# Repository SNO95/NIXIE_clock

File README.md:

# NIXIE_clock
ATmega328p and DS3231 based nixie clock.
PCBs are from JLC PCB, the first version had some errors (pictures are the first version, the battery hodlers silk screen was off by 0.5mm and the p channel mosfets in the h bridge were wired wrong, and I forgot the reset pullup on the ATmega) but I think they are fixed now. If you find anything please let me know.

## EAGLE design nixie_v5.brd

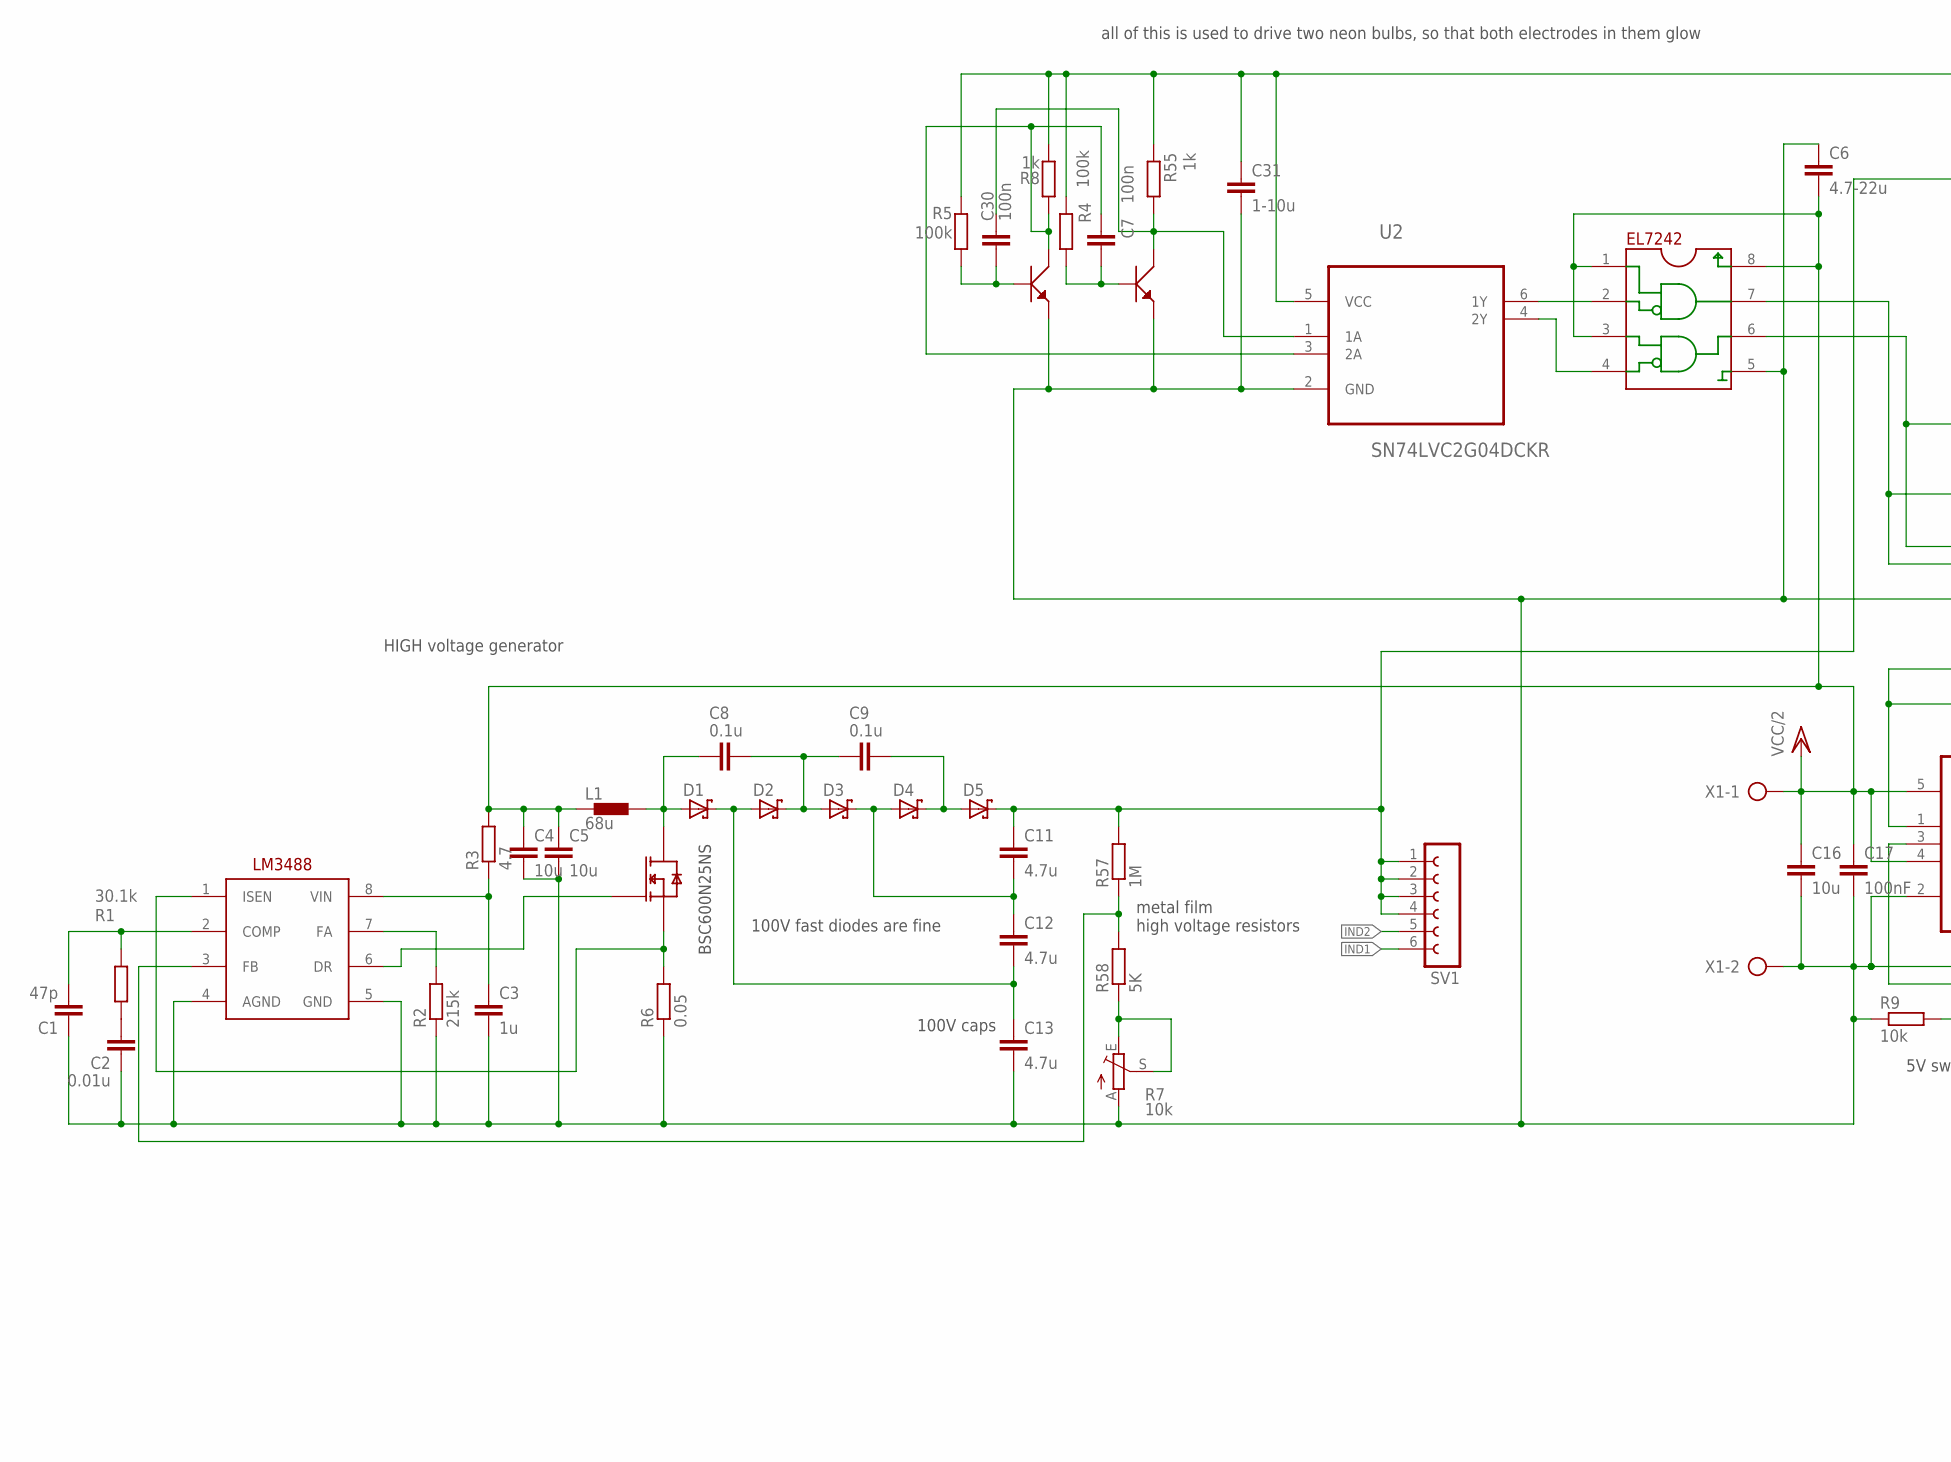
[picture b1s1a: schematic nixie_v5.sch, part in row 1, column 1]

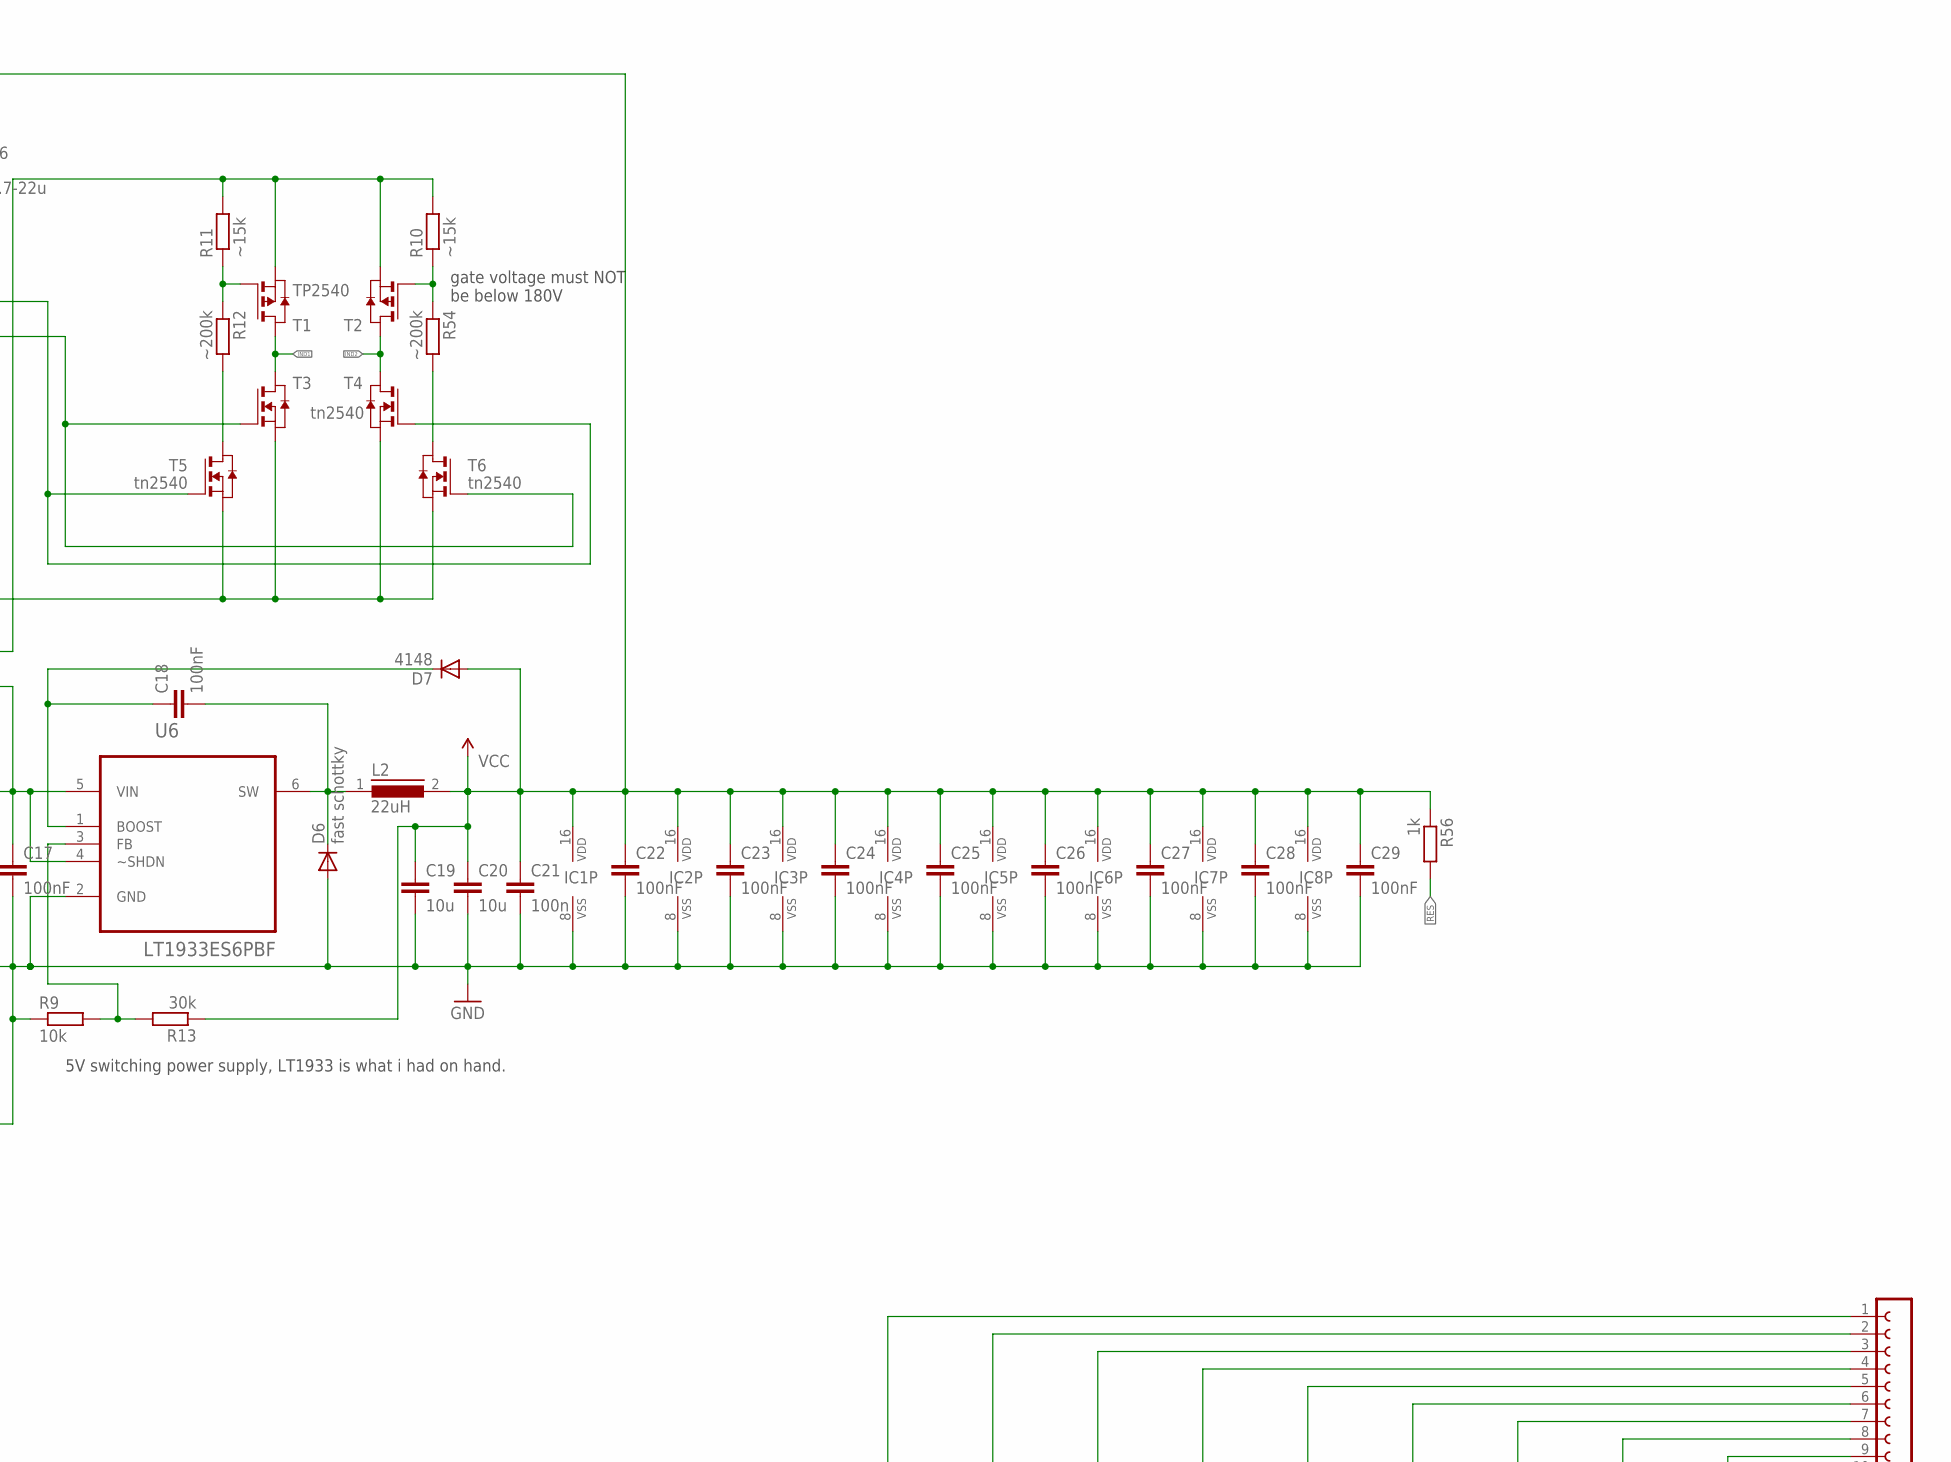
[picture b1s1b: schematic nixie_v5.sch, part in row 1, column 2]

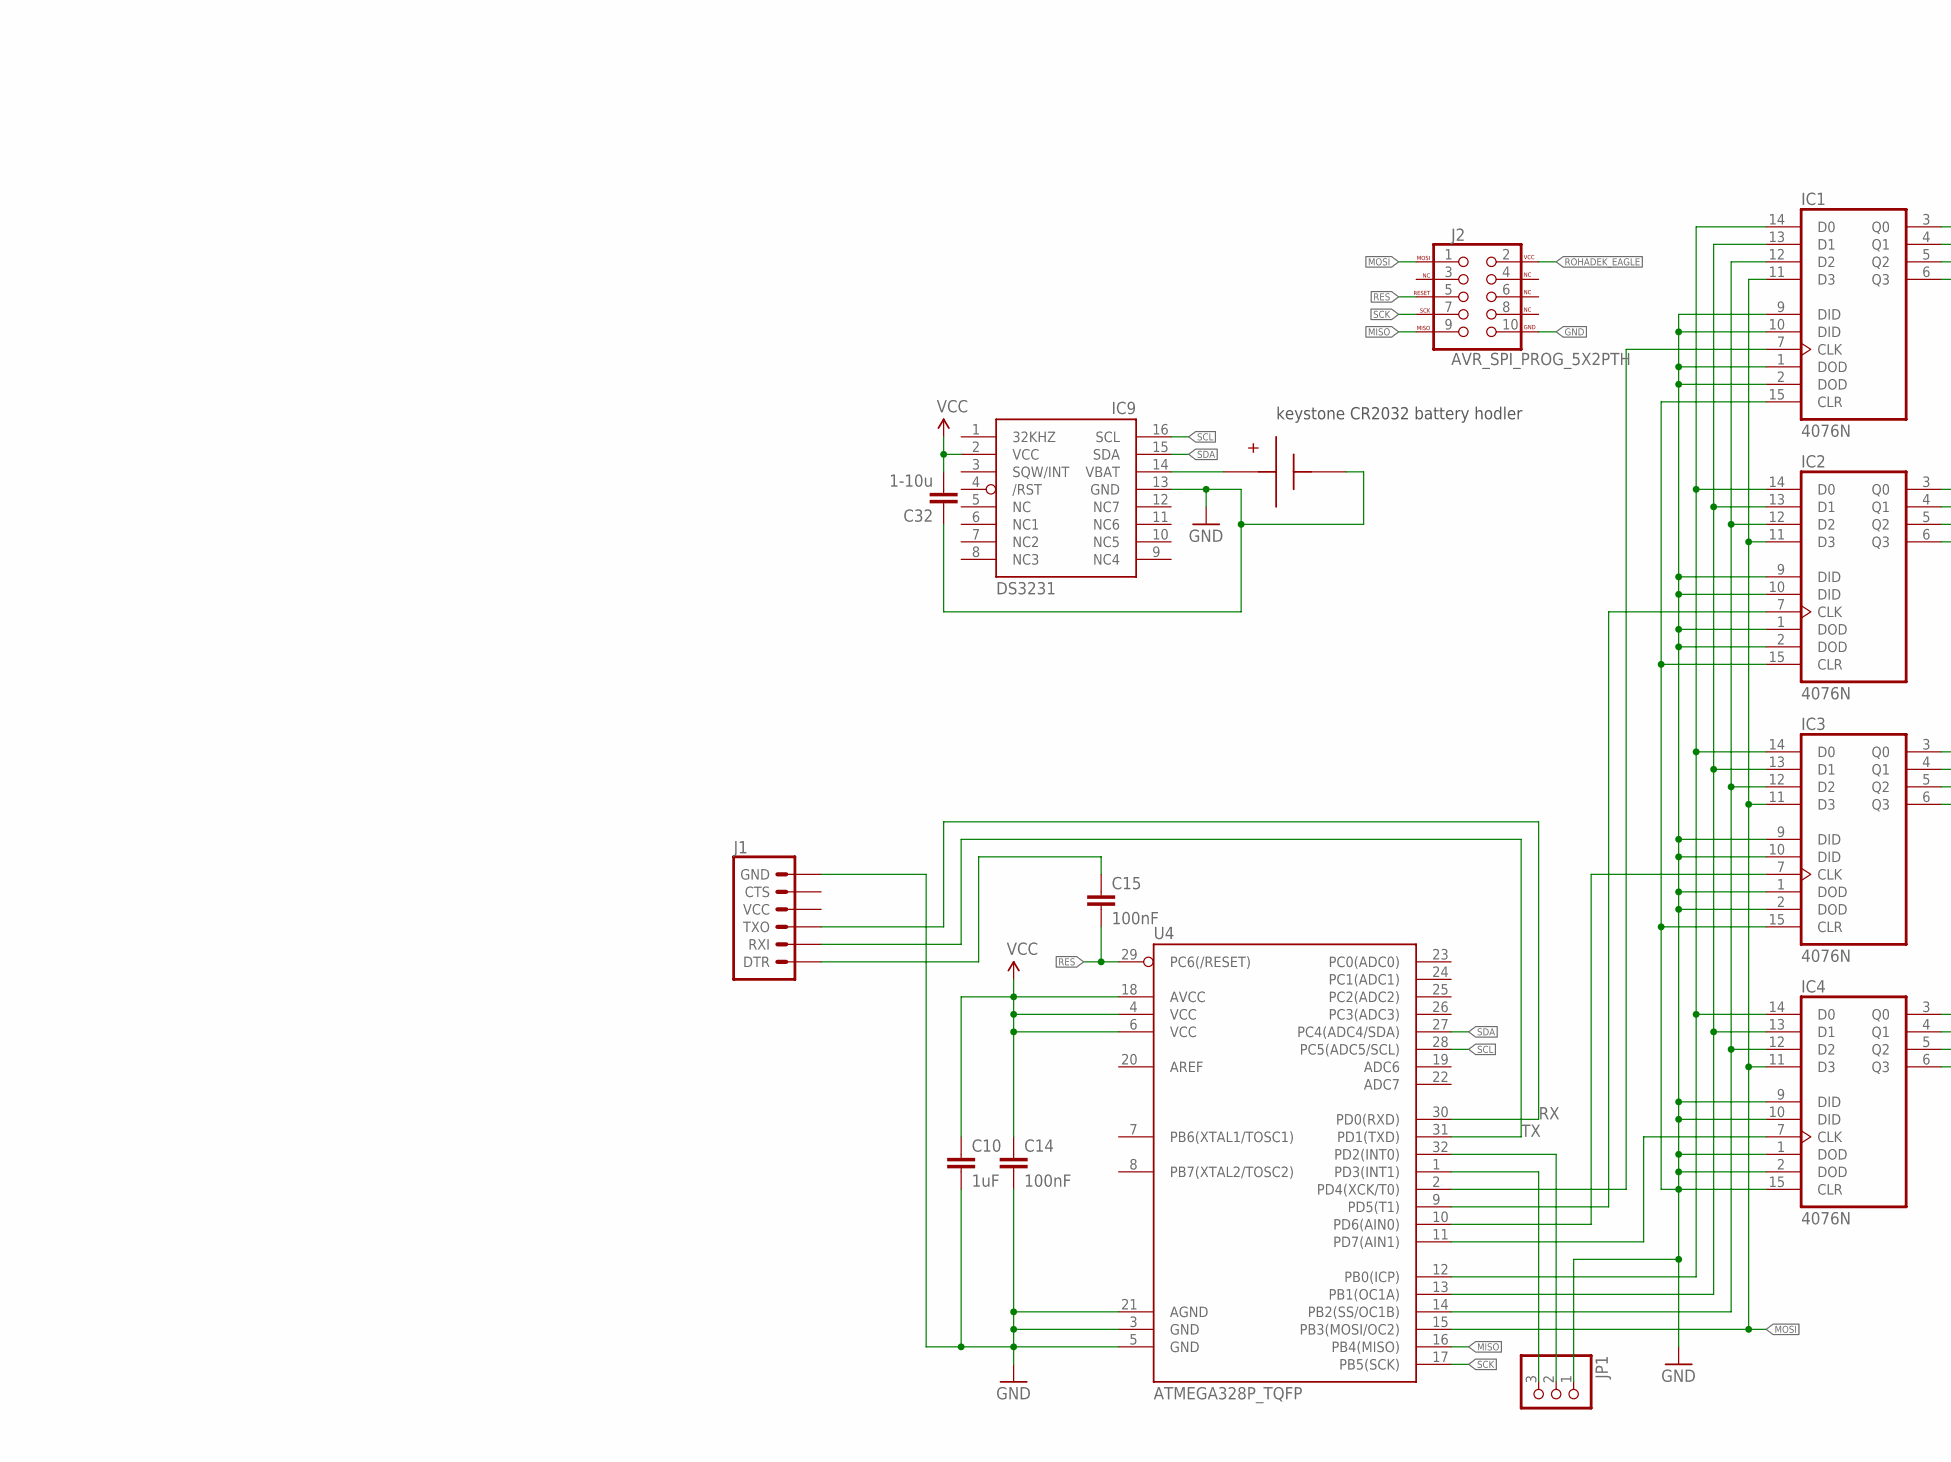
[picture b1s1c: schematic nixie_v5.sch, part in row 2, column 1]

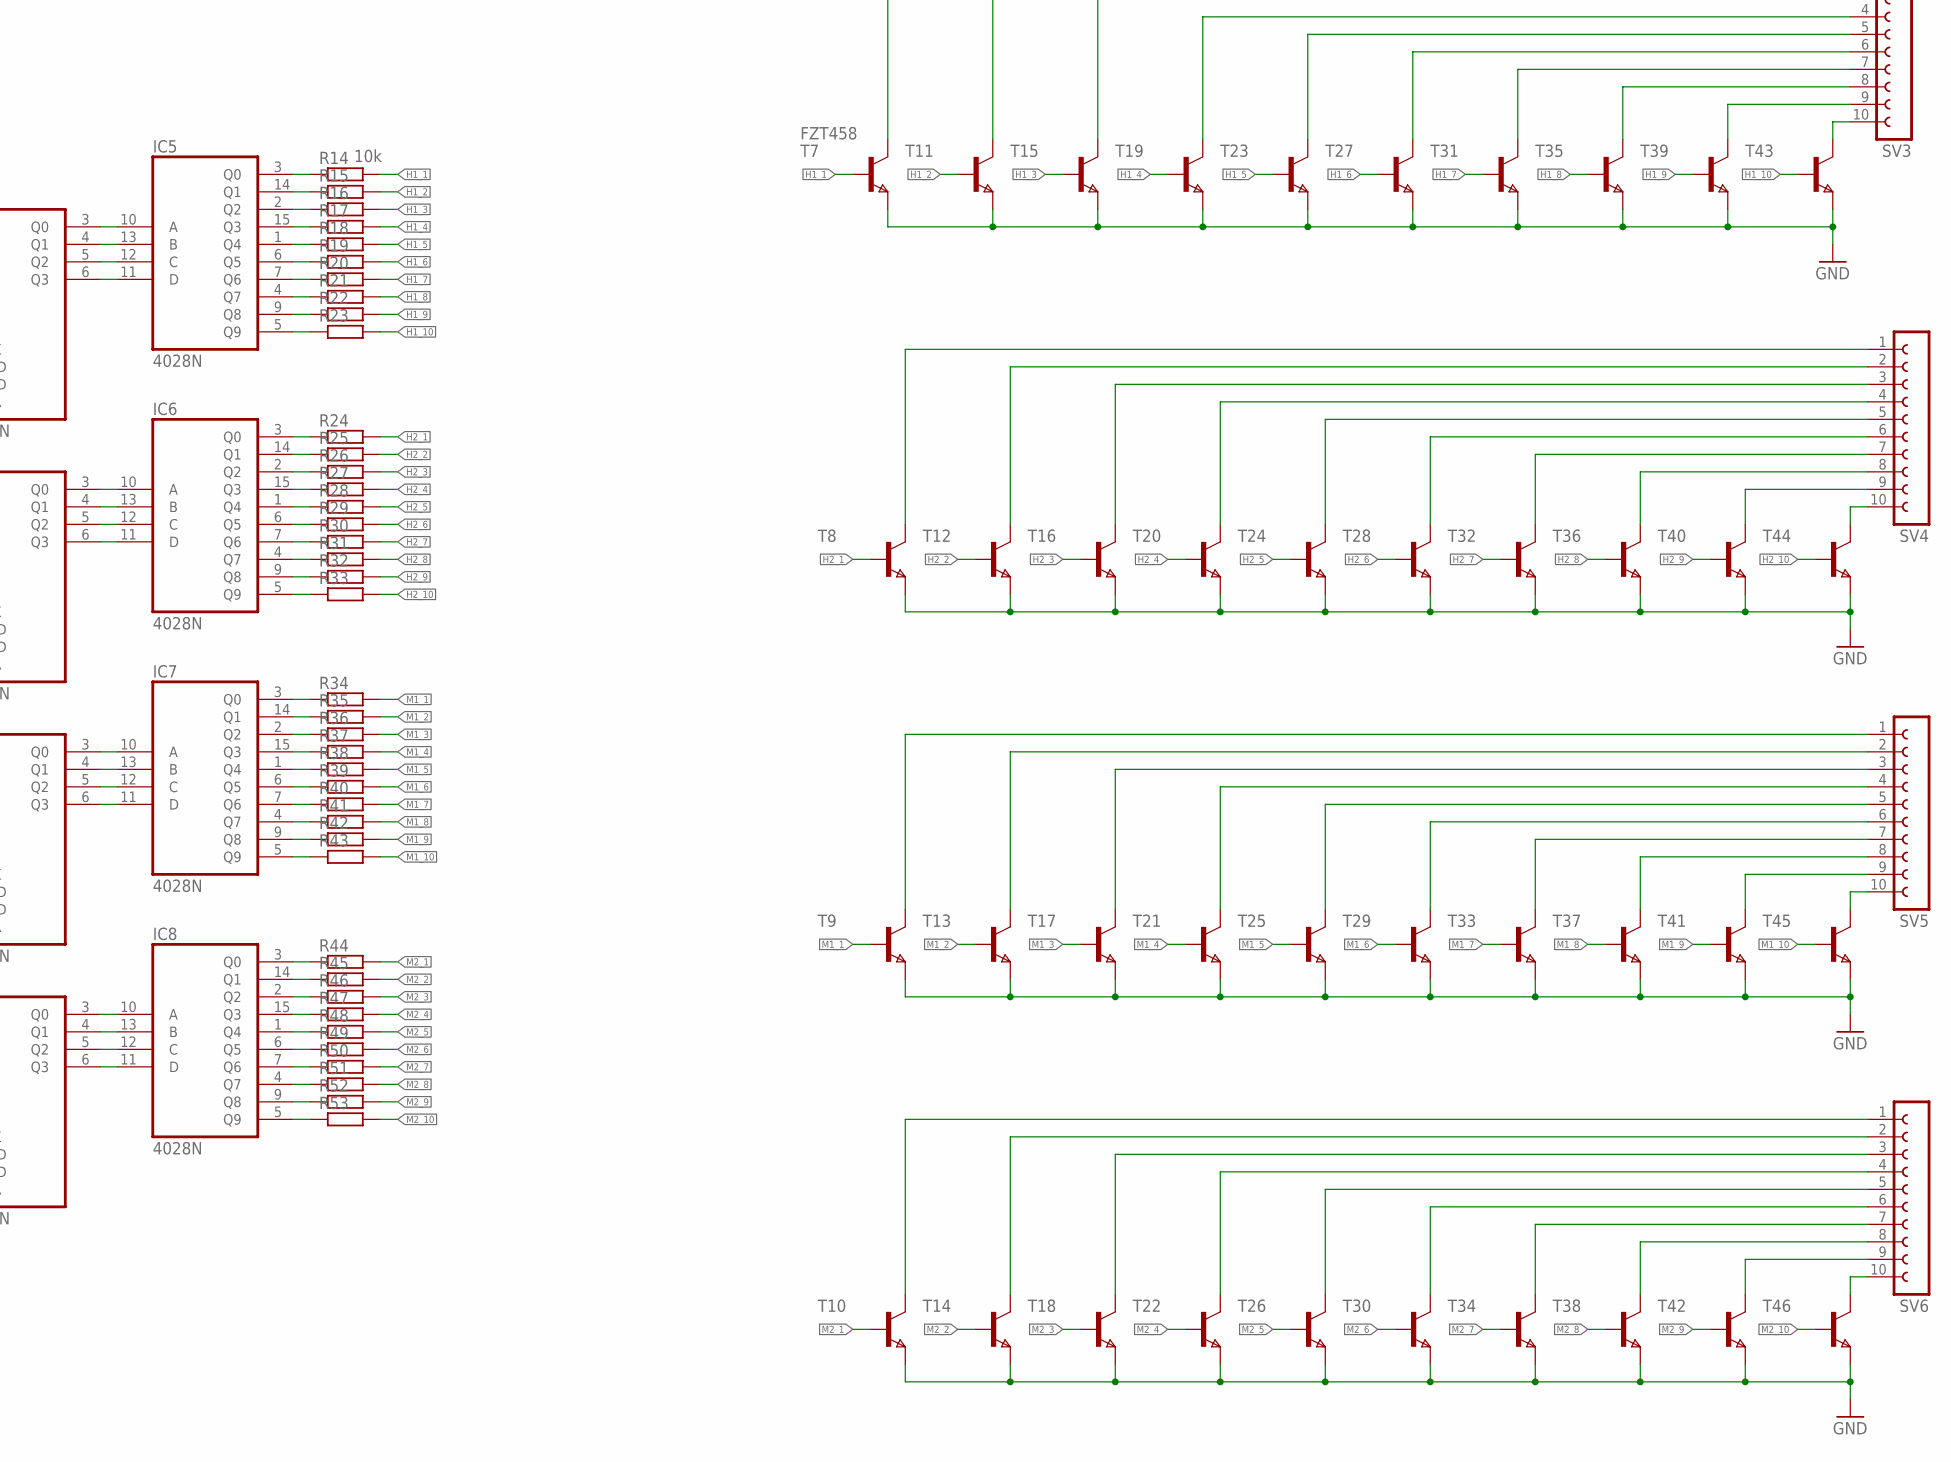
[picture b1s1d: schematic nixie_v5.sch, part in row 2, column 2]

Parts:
BSC600N25NS: BSC600N25NS; PGTDSON
C1: 47p; C0402
C2: 0.01u; C0402
C3: 1u; C0805
C4, C5, C16, C19, C20: 10u; C1206
C6: 4.7-22u; C1206
C7, C30: 100n; C0402
C8, C9: 0.1u; C0805
C10: 1uF; C0402
C11, C12, C13: 4.7u; C2220K
C14, C15: 100nF; C0402
C17, C18: 100nF; C0805K
C21: 100n; C0805K
C22, C23, C24, C25, C26, C27, C28, C29: 100nF; C0805
C31, C32: 1-10u; C0805
D1, D2, D3, D4, D5: SCHOTTKY-DIODE; POWERDI123
D6: fast schottky; SOD123
D7: 4148; SOD123
EL7242: EL7242
IC1, IC2, IC3, IC4: 4076N; DIL16
IC5, IC6, IC7, IC8: 4028N; DIL16
IC9: DS3231/SO; SO16W
J1: 6_PIN_SERIAL_TARGETLOCK; 1X06_LOCK
J2: AVR_SPI_PROG_5X2PTH; 2X5
JP1: PINHD-1X3CB; 1X03-CLEANBIG
L1: 68u; DR1030
L2: 22uH; DR74
R1: 30.1k; R0402
R2: 215k; R0402
R3: 4.7; R0805
R4, R5: 100k; R0402
R6: 0.05; R2512
R7: 10k; S64Y
R8, R55, R56: 1k; R0402
R9: 10k; M0805
R10, R11: ~15k; M0805
R12, R54: ~200k; M0805
R13: 30k; M0805
R14: 10k; M1206
R15, R16, R17, R18, R19, R20, R21, R22, R23, R24, R25, R26, R27, R28, R29, R30, R31, R32, R33, R34, R35, R36, R37, R38, R39, R40, R41, R42, R43, R44, R45, R46, R47, R48, R49, R50, R51, R52, R53: R-EU_M1206; M1206
R57: 1M; R1206
R58: 5K; R1206
SV1: FE06-1; FE06
SV3, SV4, SV5, SV6: FE10-1; FE10
T1: TP2540; SOT89
T2: tp2540; SOT89
T3, T4, T5, T6: tn2540; SOT89
T7: FZT458; SOT223
T8, T9, T10, T11, T12, T13, T14, T15, T16, T17, T18, T19, T20, T21, T22, T23, T24, T25, T26, T27, T28, T29, T30, T31, T32, T33, T34, T35, T36, T37, T38, T39, T40, T41, T42, T43, T44, T45, T46: NPNSOT223; SOT223
U1: LM3488; VSSOP-8
U2: SN74LVC2G04DCKR; SOT65P210X110-6N
U4: ATMEGA328P_TQFP; TQFP32-08
U6: LT1933ES6PBF; SOT95P280X145-6N
U$1: RTC2032; CR2032
U$2: DUAL_NPNSC; SC-70
X1: AK300/2

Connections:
CLK_H1: IC1.7 (CLK), U4.2 (PD4(XCK/T0))
CLK_H2: IC2.7 (CLK), U4.9 (PD5(T1))
CLK_M1: IC3.7 (CLK), U4.10 (PD6(AIN0))
CLK_M2: IC4.7 (CLK), U4.11 (PD7(AIN1))
D0: IC1.14 (D0), IC2.14 (D0), IC3.14 (D0), IC4.14 (D0), U4.12 (PB0(ICP))
D1: IC1.13 (D1), IC2.13 (D1), IC3.13 (D1), IC4.13 (D1), U4.13 (PB1(OC1A))
D2: IC1.12 (D2), IC2.12 (D2), IC3.12 (D2), IC4.12 (D2), U4.14 (PB2(SS/OC1B))
GND: C1.1, C2.2, C3.2, C4.2, C5.2, C6.1, C10.2, C13.2, C14.2, C16.2, C17.2, C19.2, C20.2, C21.2, C22.2, C23.2, C24.2, C25.2, C26.2, C27.2, C28.2, C29.2, C31.2, C32.1, D6.A, EL7242.5, IC1.1 (DOD), IC1.2 (DOD), IC1.8 (VSS), IC1.9 (DID), IC1.10 (DID), IC1.15 (CLR), IC2.1 (DOD), IC2.2 (DOD), IC2.8 (VSS), IC2.9 (DID), IC2.10 (DID), IC2.15 (CLR), IC3.1 (DOD), IC3.2 (DOD), IC3.8 (VSS), IC3.9 (DID), IC3.10 (DID), IC3.15 (CLR), IC4.1 (DOD), IC4.2 (DOD), IC4.8 (VSS), IC4.9 (DID), IC4.10 (DID), IC4.15 (CLR), IC5.8 (VSS), IC6.8 (VSS), IC7.8 (VSS), IC8.8 (VSS), IC9.13 (GND), J1.6 (GND), J2.10 (GND), JP1.1, R2.1, R6.1, R7.A, R9.1, T3.3 (S), T4.3 (S), T5.3 (S), T6.3 (S), T7.3 (E), T8.3 (E), T9.3 (E), T10.3 (E), T11.3 (E), T12.3 (E), T13.3 (E), T14.3 (E), T15.3 (E), T16.3 (E), T17.3 (E), T18.3 (E), T19.3 (E), T20.3 (E), T21.3 (E), T22.3 (E), T23.3 (E), T24.3 (E), T25.3 (E), T26.3 (E), T27.3 (E), T28.3 (E), T29.3 (E), T30.3 (E), T31.3 (E), T32.3 (E), T33.3 (E), T34.3 (E), T35.3 (E), T36.3 (E), T37.3 (E), T38.3 (E), T39.3 (E), T40.3 (E), T41.3 (E), T42.3 (E), T43.3 (E), T44.3 (E), T45.3 (E), T46.3 (E), U1.4 (AGND), U1.5 (GND), U2.2 (GND), U4.3 (GND), U4.5 (GND), U4.21 (AGND), U6.2 (GND), U$1.- (BATT-), U$2.1 (EMITTER), U$2.4 (EMITTER1), X1.2
H1_1: R14.2, T7.1 (B)
H1_2: R15.2, T11.1 (B)
H1_3: R16.2, T15.1 (B)
H1_4: R17.2, T19.1 (B)
H1_5: R18.2, T23.1 (B)
H1_6: R19.2, T27.1 (B)
H1_7: R20.2, T31.1 (B)
H1_8: R21.2, T35.1 (B)
H1_9: R22.2, T39.1 (B)
H1_10: R23.2, T43.1 (B)
H2_1: R24.2, T8.1 (B)
H2_2: R25.2, T12.1 (B)
H2_3: R26.2, T16.1 (B)
H2_4: R27.2, T20.1 (B)
H2_5: R28.2, T24.1 (B)
H2_6: R29.2, T28.1 (B)
H2_7: R30.2, T32.1 (B)
H2_8: R31.2, T36.1 (B)
H2_9: R32.2, T40.1 (B)
H2_10: R33.2, T44.1 (B)
INC: JP1.3, U4.1 (PD3(INT1))
IND1: SV1.6, T1.2 (D), T3.2 (D), T3.2@1 (D)
IND2: SV1.5, T2.2 (D), T4.2 (D), T4.2@1 (D)
M1_1: R34.2, T9.1 (B)
M1_2: R35.2, T13.1 (B)
M1_3: R36.2, T17.1 (B)
M1_4: R37.2, T21.1 (B)
M1_5: R38.2, T25.1 (B)
M1_6: R39.2, T29.1 (B)
M1_7: R40.2, T33.1 (B)
M1_8: R41.2, T37.1 (B)
M1_9: R42.2, T41.1 (B)
M1_10: R43.2, T45.1 (B)
M2_1: R44.2, T10.1 (B)
M2_2: R45.2, T14.1 (B)
M2_3: R46.2, T18.1 (B)
M2_4: R47.2, T22.1 (B)
M2_5: R48.2, T26.1 (B)
M2_6: R49.2, T30.1 (B)
M2_7: R50.2, T34.1 (B)
M2_8: R51.2, T38.1 (B)
M2_9: R52.2, T42.1 (B)
M2_10: R53.2, T46.1 (B)
MISO: J2.9 (MISO), U4.16 (PB4(MISO))
MOSI: IC1.11 (D3), IC2.11 (D3), IC3.11 (D3), IC4.11 (D3), J2.1 (MOSI), U4.15 (PB3(MOSI/OC2))
unnamed: IC9.14 (VBAT), U$1.+ (BATT+)
unnamed: R11.1, R12.1, T1.1 (G)
unnamed: R7.E, R7.S, R58.1
unnamed: IC1.3 (Q0), IC5.10 (A)
unnamed: IC1.6 (Q3), IC5.11 (D)
unnamed: IC1.5 (Q2), IC5.12 (C)
unnamed: IC1.4 (Q1), IC5.13 (B)
unnamed: IC2.3 (Q0), IC6.10 (A)
unnamed: IC2.6 (Q3), IC6.11 (D)
unnamed: IC2.5 (Q2), IC6.12 (C)
unnamed: IC2.4 (Q1), IC6.13 (B)
unnamed: IC3.3 (Q0), IC7.10 (A)
unnamed: IC3.6 (Q3), IC7.11 (D)
unnamed: IC3.5 (Q2), IC7.12 (C)
unnamed: IC3.4 (Q1), IC7.13 (B)
unnamed: IC4.3 (Q0), IC8.10 (A)
unnamed: IC4.6 (Q3), IC8.11 (D)
unnamed: IC4.5 (Q2), IC8.12 (C)
unnamed: IC4.4 (Q1), IC8.13 (B)
unnamed: SV3.1, T7.2 (C), T7.4 (C)
unnamed: SV3.2, T11.2 (C), T11.4 (C)
unnamed: C18.1, D7.C, U6.1 (BOOST)
unnamed: SV3.3, T15.2 (C), T15.4 (C)
unnamed: SV3.4, T19.2 (C), T19.4 (C)
unnamed: SV3.5, T23.2 (C), T23.4 (C)
unnamed: SV3.6, T27.2 (C), T27.4 (C)
unnamed: SV3.7, T31.2 (C), T31.4 (C)
unnamed: SV3.8, T35.2 (C), T35.4 (C)
unnamed: SV3.9, T39.2 (C), T39.4 (C)
unnamed: SV3.10, T43.2 (C), T43.4 (C)
unnamed: C3.1, R3.1, U1.8 (VIN)
unnamed: IC5.3 (Q0), R14.1
unnamed: IC5.14 (Q1), R15.1
unnamed: IC5.2 (Q2), R16.1
unnamed: IC5.15 (Q3), R17.1
unnamed: IC5.1 (Q4), R18.1
unnamed: IC5.6 (Q5), R19.1
unnamed: IC5.7 (Q6), R20.1
unnamed: IC5.4 (Q7), R21.1
unnamed: IC5.9 (Q8), R22.1
unnamed: IC5.5 (Q9), R23.1
unnamed: IC6.3 (Q0), R24.1
unnamed: IC6.14 (Q1), R25.1
unnamed: IC6.2 (Q2), R26.1
unnamed: IC6.15 (Q3), R27.1
unnamed: IC6.1 (Q4), R28.1
unnamed: IC6.6 (Q5), R29.1
unnamed: IC6.7 (Q6), R30.1
unnamed: IC6.4 (Q7), R31.1
unnamed: IC6.9 (Q8), R32.1
unnamed: IC6.5 (Q9), R33.1
unnamed: SV4.1, T8.2 (C), T8.4 (C)
unnamed: SV4.2, T12.2 (C), T12.4 (C)
unnamed: SV4.3, T16.2 (C), T16.4 (C)
unnamed: SV4.4, T20.2 (C), T20.4 (C)
unnamed: SV4.5, T24.2 (C), T24.4 (C)
unnamed: SV4.6, T28.2 (C), T28.4 (C)
unnamed: SV4.7, T32.2 (C), T32.4 (C)
unnamed: SV4.8, T36.2 (C), T36.4 (C)
unnamed: SV4.9, T40.2 (C), T40.4 (C)
unnamed: SV4.10, T44.2 (C), T44.4 (C)
unnamed: IC8.3 (Q0), R44.1
unnamed: IC8.14 (Q1), R45.1
unnamed: IC8.2 (Q2), R46.1
unnamed: IC8.15 (Q3), R47.1
unnamed: IC8.1 (Q4), R48.1
unnamed: IC8.6 (Q5), R49.1
unnamed: IC8.7 (Q6), R50.1
unnamed: IC8.4 (Q7), R51.1
unnamed: IC8.9 (Q8), R52.1
unnamed: IC8.5 (Q9), R53.1
unnamed: IC7.3 (Q0), R34.1
unnamed: IC7.14 (Q1), R35.1
unnamed: IC7.2 (Q2), R36.1
unnamed: IC7.15 (Q3), R37.1
unnamed: IC7.1 (Q4), R38.1
unnamed: IC7.6 (Q5), R39.1
unnamed: IC7.7 (Q6), R40.1
unnamed: IC7.4 (Q7), R41.1
unnamed: IC7.9 (Q8), R42.1
unnamed: IC7.5 (Q9), R43.1
unnamed: R9.2, R13.2, U6.3 (FB)
unnamed: BSC600N25NS.DRAIN, C8.2, D1.A, L1.2
unnamed: R2.2, U1.7 (FA)
unnamed: BSC600N25NS.GATE, U1.6 (DR)
unnamed: BSC600N25NS.SOURCE, BSC600N25NS.SOURCE1 (SOURCE), BSC600N25NS.SOURCE3 (SOURCE), R6.2, U1.1 (ISEN)
unnamed: C8.1, C9.2, D2.K (C), D3.A
unnamed: C9.1, D4.K (C), D5.A
unnamed: C12.2, C13.1, D1.K (C), D2.A
unnamed: SV5.1, T9.2 (C), T9.4 (C)
unnamed: SV5.2, T13.2 (C), T13.4 (C)
unnamed: SV5.3, T17.2 (C), T17.4 (C)
unnamed: SV5.4, T21.2 (C), T21.4 (C)
unnamed: SV5.5, T25.2 (C), T25.4 (C)
unnamed: SV5.6, T29.2 (C), T29.4 (C)
unnamed: SV5.7, T33.2 (C), T33.4 (C)
unnamed: SV5.8, T37.2 (C), T37.4 (C)
unnamed: SV5.9, T41.2 (C), T41.4 (C)
unnamed: SV5.10, T45.2 (C), T45.4 (C)
unnamed: SV6.1, T10.2 (C), T10.4 (C)
unnamed: SV6.2, T14.2 (C), T14.4 (C)
unnamed: SV6.3, T18.2 (C), T18.4 (C)
unnamed: SV6.4, T22.2 (C), T22.4 (C)
unnamed: SV6.5, T26.2 (C), T26.4 (C)
unnamed: SV6.6, T30.2 (C), T30.4 (C)
unnamed: SV6.7, T34.2 (C), T34.4 (C)
unnamed: SV6.8, T38.2 (C), T38.4 (C)
unnamed: SV6.9, T42.2 (C), T42.4 (C)
unnamed: SV6.10, T46.2 (C), T46.4 (C)
unnamed: C11.2, C12.1, D3.K (C), D4.A
unnamed: C1.2, R1.2, U1.2 (COMP)
unnamed: R57.1, R58.2, U1.3 (FB)
unnamed: C2.1, R1.1
unnamed: C15.1, J1.1 (DTR)
unnamed: R10.1, R54.1, T2.1 (G)
unnamed: EL7242.6, T3.1 (G), T6.1 (G)
unnamed: C30.2, R5.2, U$2.2 (BASE)
unnamed: C7.2, R4.2, U$2.5 (BASE1)
unnamed: C7.1, R8.2, U2.3 (2A), U$2.6 (COLLECTOR)
unnamed: R12.2, T5.2 (D), T5.2@1 (D)
unnamed: R54.2, T6.2 (D), T6.2@1 (D)
unnamed: C30.1, R55.2, U2.1 (1A), U$2.3 (COLLECTOR1)
unnamed: EL7242.7, T4.1 (G), T5.1 (G)
unnamed: C11.1, D5.K (C), R10.2, R11.2, R57.2, SV1.1, SV1.2, SV1.3, SV1.4, T1.3 (S), T2.3 (S)
unnamed: EL7242.2, U2.6 (1Y)
unnamed: EL7242.4, U2.4 (2Y)
NC: J2.4 (NC), J2.6 (NC), J2.8 (NC)
RES: C15.2, J2.5 (RESET), R56.2, U4.29 (PC6(/RESET))
ROHADEK_EAGLE: J2.2 (VCC)
RX: J1.3 (TXO), U4.30 (PD0(RXD))
SCK: J2.7 (SCK), U4.17 (PB5(SCK))
SCL: IC9.16 (SCL), U4.28 (PC5(ADC5/SCL))
SDA: IC9.15 (SDA), U4.27 (PC4(ADC4/SDA))
SET: JP1.2, U4.32 (PD2(INT0))
SW: C18.2, D6.C, L2.1, U6.6 (SW)
TX: J1.2 (RXI), U4.31 (PD1(TXD))
VCC: C10.1, C14.1, C19.1, C20.1, C21.1, C22.1, C23.1, C24.1, C25.1, C26.1, C27.1, C28.1, C29.1, C31.1, C32.2, D7.A, IC1.16 (VDD), IC2.16 (VDD), IC3.16 (VDD), IC4.16 (VDD), IC5.16 (VDD), IC6.16 (VDD), IC7.16 (VDD), IC8.16 (VDD), IC9.2 (VCC), L2.2, R4.1, R5.1, R8.1, R13.1, R55.1, R56.1, U2.5 (VCC), U4.4 (VCC), U4.6 (VCC), U4.18 (AVCC)
VCC/2: C4.1, C5.1, C6.2, C16.1, C17.1, EL7242.1, EL7242.3, EL7242.8, L1.1, R3.2, U6.4 (~SHDN), U6.5 (VIN), X1.1

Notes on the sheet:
gate voltage must NOT be below 180V
all of this is used to drive two neon bulbs, so that both electrodes in them glow
5V switching power supply, LT1933 is what i had on hand.
HIGH voltage generator
metal film high voltage resistors
BSC600N25NS
100V fast diodes are fine
100V caps
keystone CR2032 battery hodler

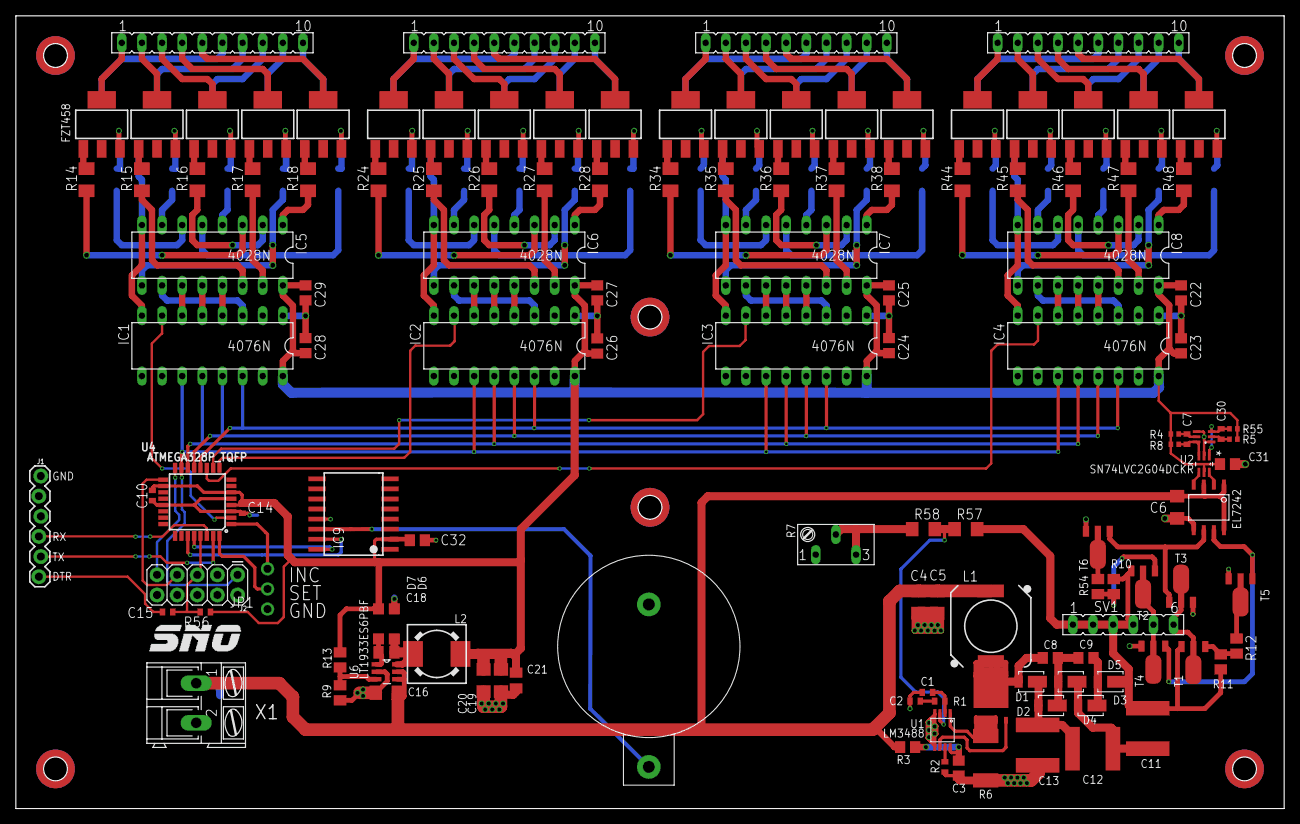
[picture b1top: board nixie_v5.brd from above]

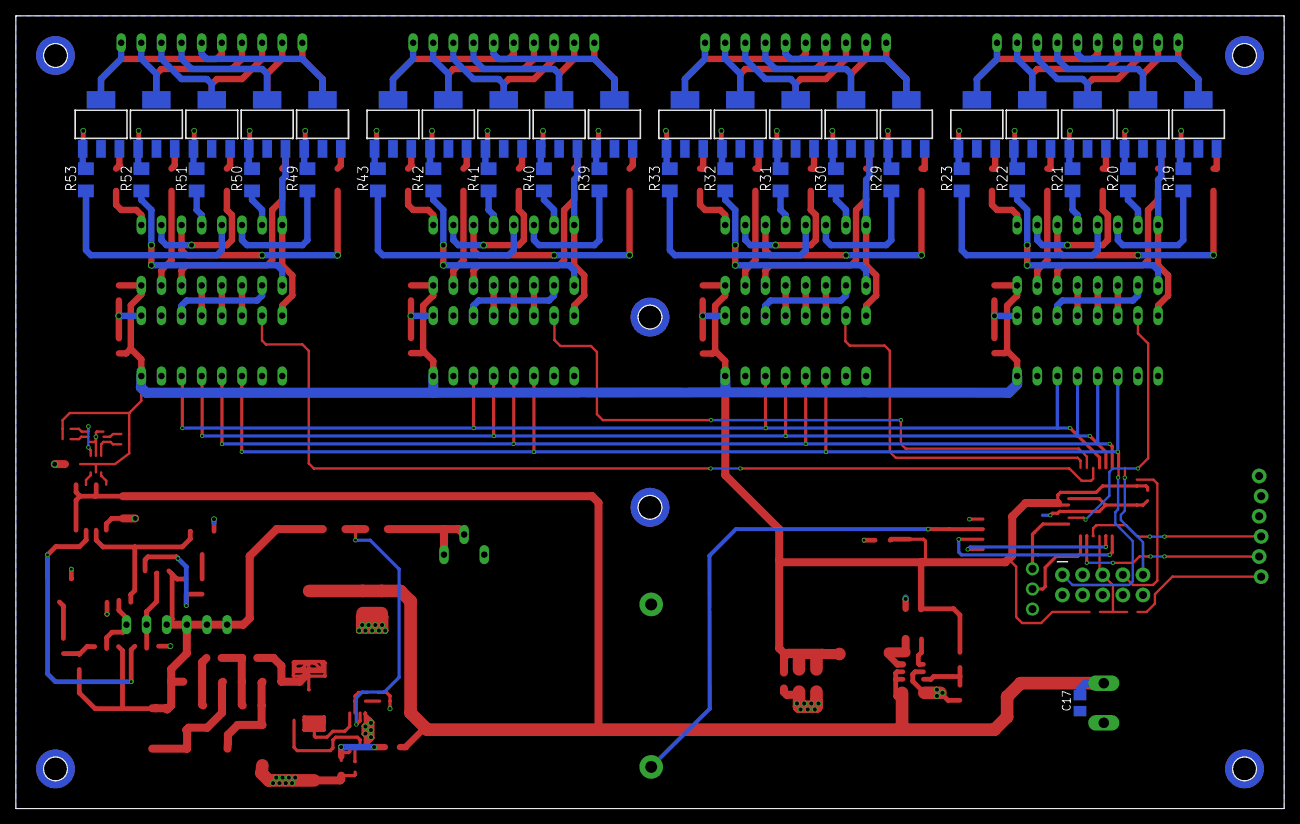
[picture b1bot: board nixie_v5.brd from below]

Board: 2 copper layers, 160.0 x 100.0 mm, 171 parts (41 on the bottom side), 190 nets.

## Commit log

2023-12-30 3d printable case files

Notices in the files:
parts and their libraries:
SparkFun-IC-Microcontroller: Licensing: Creative Commons ShareAlike 4.0 International - https://creativecommons.org/licenses/by-sa/4.0
